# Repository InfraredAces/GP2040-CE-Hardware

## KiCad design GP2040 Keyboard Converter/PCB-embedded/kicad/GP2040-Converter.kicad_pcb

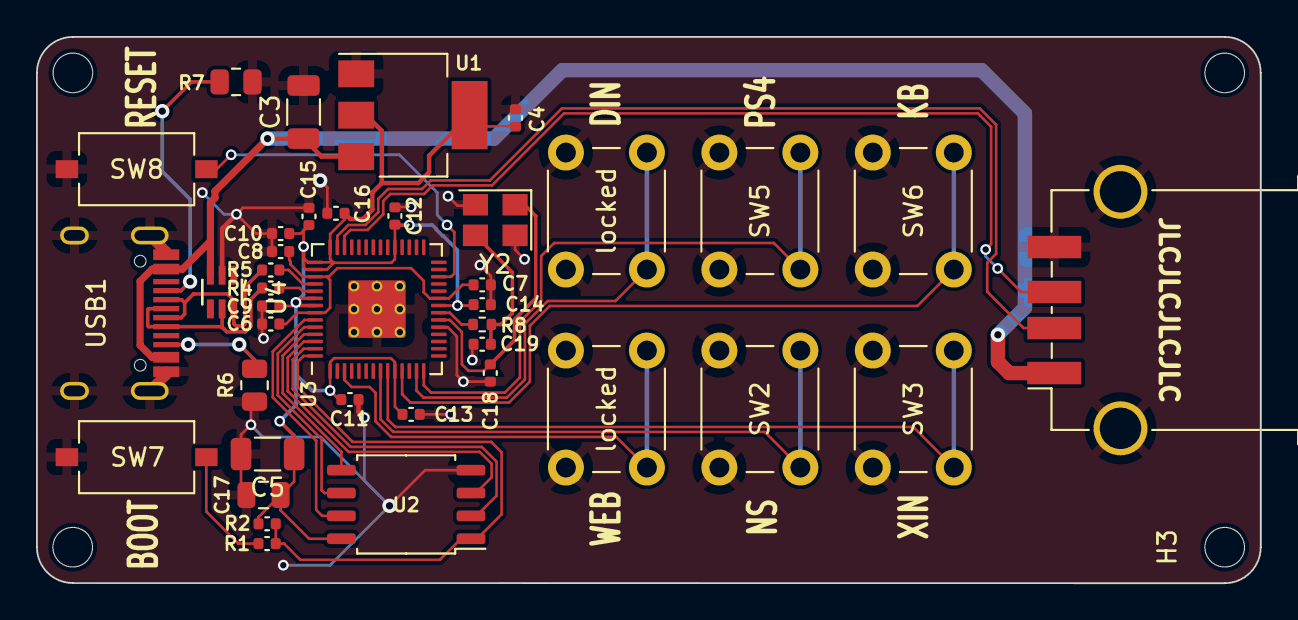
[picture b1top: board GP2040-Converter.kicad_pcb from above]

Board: 2 copper layers, 68.0 x 30.4 mm, 43 parts (0 on the bottom side), 29 nets.

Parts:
C3, C5: 10u; C_1206_3216Metric
C4, C6, C7, C9, C11, C12, C13, C14, C15, C16: 100n; C_0402_1005Metric
C8, C10: 1u; C_0402_1005Metric
C17: 10u; C_0805_2012Metric
C18, C19: 30p; C_0402_1005Metric
H1, H2, H3, H4: MountingHole; MountingHole_2.2mm_M2
J1: USB_A; USB_A_TE_292303-7_Horizontal
R1: 1k; C_0402_1005Metric
R2: 10k; C_0402_1005Metric
R4, R5: 27; C_0402_1005Metric
R6, R7: 5.1k; R_0805_2012Metric
R8: 1k; R_0402_1005Metric
SW2, SW3, SW5, SW6: SW_Push_Open; SW_PUSH_6mm_H13mm
SW7, SW8: SW_Push_Open; SW_Tactile_SPST_NO_Straight_CK_PTS636Sx25SMTRLFS
U1: NCP1117-3.3_SOT223; SOT-223-3_TabPin2
U2: W25Q128JVS; SOIC-8_5.23x5.23mm_P1.27mm
U3: RP2040; RP2040-QFN-56
U4: SMF05CT1G; SOT65P210X110-6N
USB1: HRO-TYPE-C-31-M-12; HRO-TYPE-C-31-M-12-Assembly
Y2: Crystal_GND24; Crystal_SMD_3225-4Pin_3.2x2.5mm
locked: locked; SW_PUSH_6mm_H13mm
locked#2: SW_Push_Open; SW_PUSH_6mm_H13mm

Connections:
+1V1: C6.1, C7.1, C8.1, U3.23 (DVDD), U3.45 (VREG_VOUT), U3.50 (DVDD)
+3V3: C4.1, C5.1, C9.1, C10.1, C11.1, C12.1, C13.1, C14.1, C15.1, C16.1, C17.1, R2.1, U1.2 (VO), U2.8 (VCC), U3.1 (IOVDD), U3.10 (IOVDD), U3.22 (IOVDD), U3.33 (IOVDD), U3.42 (IOVDD), U3.43 (ADC_AVDD), U3.44 (VREG_IN), U3.48 (USB_VDD), U3.49 (IOVDD)
+5V: C3.1, J1.1 (VBUS), U1.3 (VI), U4.3, USB1.2 (VBUS), USB1.11 (VBUS)
/QSPI_SCLK: U2.6 (CLK), U3.52 (QSPI_SCLK)
/QSPI_SD0: U2.5 (DI(IO0)), U3.53 (QSPI_SD0)
/QSPI_SD1: U2.2 (DO(IO1)), U3.55 (QSPI_SD1)
/QSPI_SD2: U2.3 (IO2), U3.54 (QSPI_SD2)
/QSPI_SD3: U2.7 (IO3), U3.51 (QSPI_SD3)
/QSPI_SS: R1.1, R2.2, U2.1 (~CS), U3.56 (QSPI_SS)
/RUN: SW8.2 (B), U3.26 (RUN)
/USB_D+: R4.1, U4.5, USB1.6 (DP1), USB1.8 (DP2)
/USB_D-: R5.1, U4.6, USB1.5 (DN2), USB1.7 (DN1)
/XIN: C18.2, U3.20 (XIN), Y2.1
/XOUT: R8.2, U3.21 (XOUT)
/~USB_BOOT: R1.2, SW7.2 (B)
CIRCLE: SW3.1 (A), U3.9 (GPIO7)
CROSS: SW2.1 (A), U3.8 (GPIO6)
D_M: J1.2 (D-), U3.41 (GPIO29_ADC3)
D_P: J1.3 (D+), U3.40 (GPIO28_ADC2)
GND: C3.2, C4.2, C5.2, C6.2, C7.2, C8.2, C9.2, C10.2, C11.2, C12.2, C13.2, C14.2, C15.2, C16.2, C17.2, C18.1, C19.2, J1.4 (GND), J1.5 (Shield), R6.2, R7.2, SW2.2 (B), SW3.2 (B), SW5.2 (B), SW6.2 (B), SW7.1 (A), SW8.1 (A), U1.1 (GND), U2.4 (GND), U3.19 (TESTEN), U3.57 (GND), U4.2, USB1.1 (GND), USB1.12 (GND), USB1.13 (SHIELD), Y2.2, Y2.4, locked.2 (B), locked#2.2 (B)
unnamed: C19.1, R8.1, Y2.3
unnamed: R5.2, U3.46 (USB_DM)
unnamed: R4.2, U3.47 (USB_DP)
unnamed: R7.1, USB1.4 (CC1)
unnamed: R6.1, USB1.10 (CC2)
OPTION: U3.3 (GPIO1), locked#2.1 (A)
R2: SW6.1 (A), U3.11 (GPIO8)
SQUARE: U3.13 (GPIO10), locked.1 (A)
TRIANGLE: SW5.1 (A), U3.14 (GPIO11)

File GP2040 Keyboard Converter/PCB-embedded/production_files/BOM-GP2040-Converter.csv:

Comment,Designator,Footprint,LCSC
10u,"C17,C19",C_0805_2012Metric,C1046
10k,R2,C_0402_1005Metric,C11616
1k,R1,C_0402_1005Metric,C11702
10u,"C3,C5",C_1206_3216Metric,C13585
5.1k,"R6,R7",R_0805_2012Metric,C144553
100n,"C11,C12,C13,C14,C15,C16,C4,C6,C7,C9",C_0402_1005Metric,C1525
30p,C18,C_0402_1005Metric,C1570
SMF05CT1G,U4,SOT65P210X110-6N,C15879
HRO-TYPE-C-31-M-12,USB1,HRO-TYPE-C-31-M-12-Assembly,C165948
NCP1117-3.3_SOT223,U1,SOT-223-3_TabPin2,C185806
RP2040,U3,RP2040-QFN-56,C2040
27,"R4,R5,R8",C_0402_1005Metric,C25100
SW_Push_Open,"SW7,SW8",SW_Tactile_SPST_NO_Straight_CK_PTS636Sx25SMTRLFS,C329185
USB_A,J1,USB_A_TE_292303-7_Horizontal,C42641
1u,"C10,C8",C_0402_1005Metric,C52923
SW_Push_Open,"SW1,SW2,SW3,SW4,SW5,SW6",SW_PUSH_6mm_H13mm,C557902
Crystal_GND24,Y2,Crystal_SMD_3225-4Pin_3.2x2.5mm,C9002
W25Q128JVS,U2,SOIC-8_5.23x5.23mm_P1.27mm,C97521
MountingHole,H4,MountingHole_2.2mm_M2,
MountingHole,H1,MountingHole_2.2mm_M2,
MountingHole,H3,MountingHole_2.2mm_M2,
MountingHole,H2,MountingHole_2.2mm_M2,

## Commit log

2023-08-12 Change LDO and LDO capacitors
